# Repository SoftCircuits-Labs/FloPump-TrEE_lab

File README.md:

<h1 align="center">AirFlo-pump</h1>

## About the  AirFlo-Pump Device
It is an air sampler device built for use in the applications that require a regulated air flow, for example sampling of VOCs from plants, room etc., or to generate a regulaed air flow in wind-tunnel experiments.

## Contents
<!---List file contents of the project, in table.--->

| File/folder | Description |
|-------------|-------------|
| `AFC-CODE`       | Firmware for the device |
| `AFC-DOCS`       | Device Images, User's Guide and other documents related to the device|
| `AFC-ENCLOSURE`        | 3D Design files and DXF files for the enclosure |
| `AFC-PCB`         | PCB Schematic files, board files and Gerber files |
| `LICENSE`   | The license for the project. |
| `README.md` | This README file. |

## Built With
* [![Arduino][Arduino-l]][Arduino-url]
* [![Eagle][Eagle-l]][Eagle-url]
* [![Inventor][Inventor-l]][Inventor-url]

## Usage

## Contact 

<!-- MARKDOWN LINKS & IMAGES -->
<!-- https://www.markdownguide.org/basic-syntax/#reference-style-links -->

[Arduino-l]: https://img.shields.io/badge/arduino-00878F?style=for-the-badge&logo=arduino&logoColor=white
[Arduino-url]: https://www.arduino.cc/
[Eagle-l]: https://img.shields.io/badge/Autodesk_Eagle-000000?style=for-the-badge&logo=autodesk&logoColor=white
[Eagle-url]: https://www.autodesk.in/products/eagle/overview
[Inventor-l]: https://img.shields.io/badge/Autodesk_Inventor-000000?style=for-the-badge&logo=autodesk&logoColor=white
[Inventor-url]: https://www.autodesk.in/products/inventor/overview

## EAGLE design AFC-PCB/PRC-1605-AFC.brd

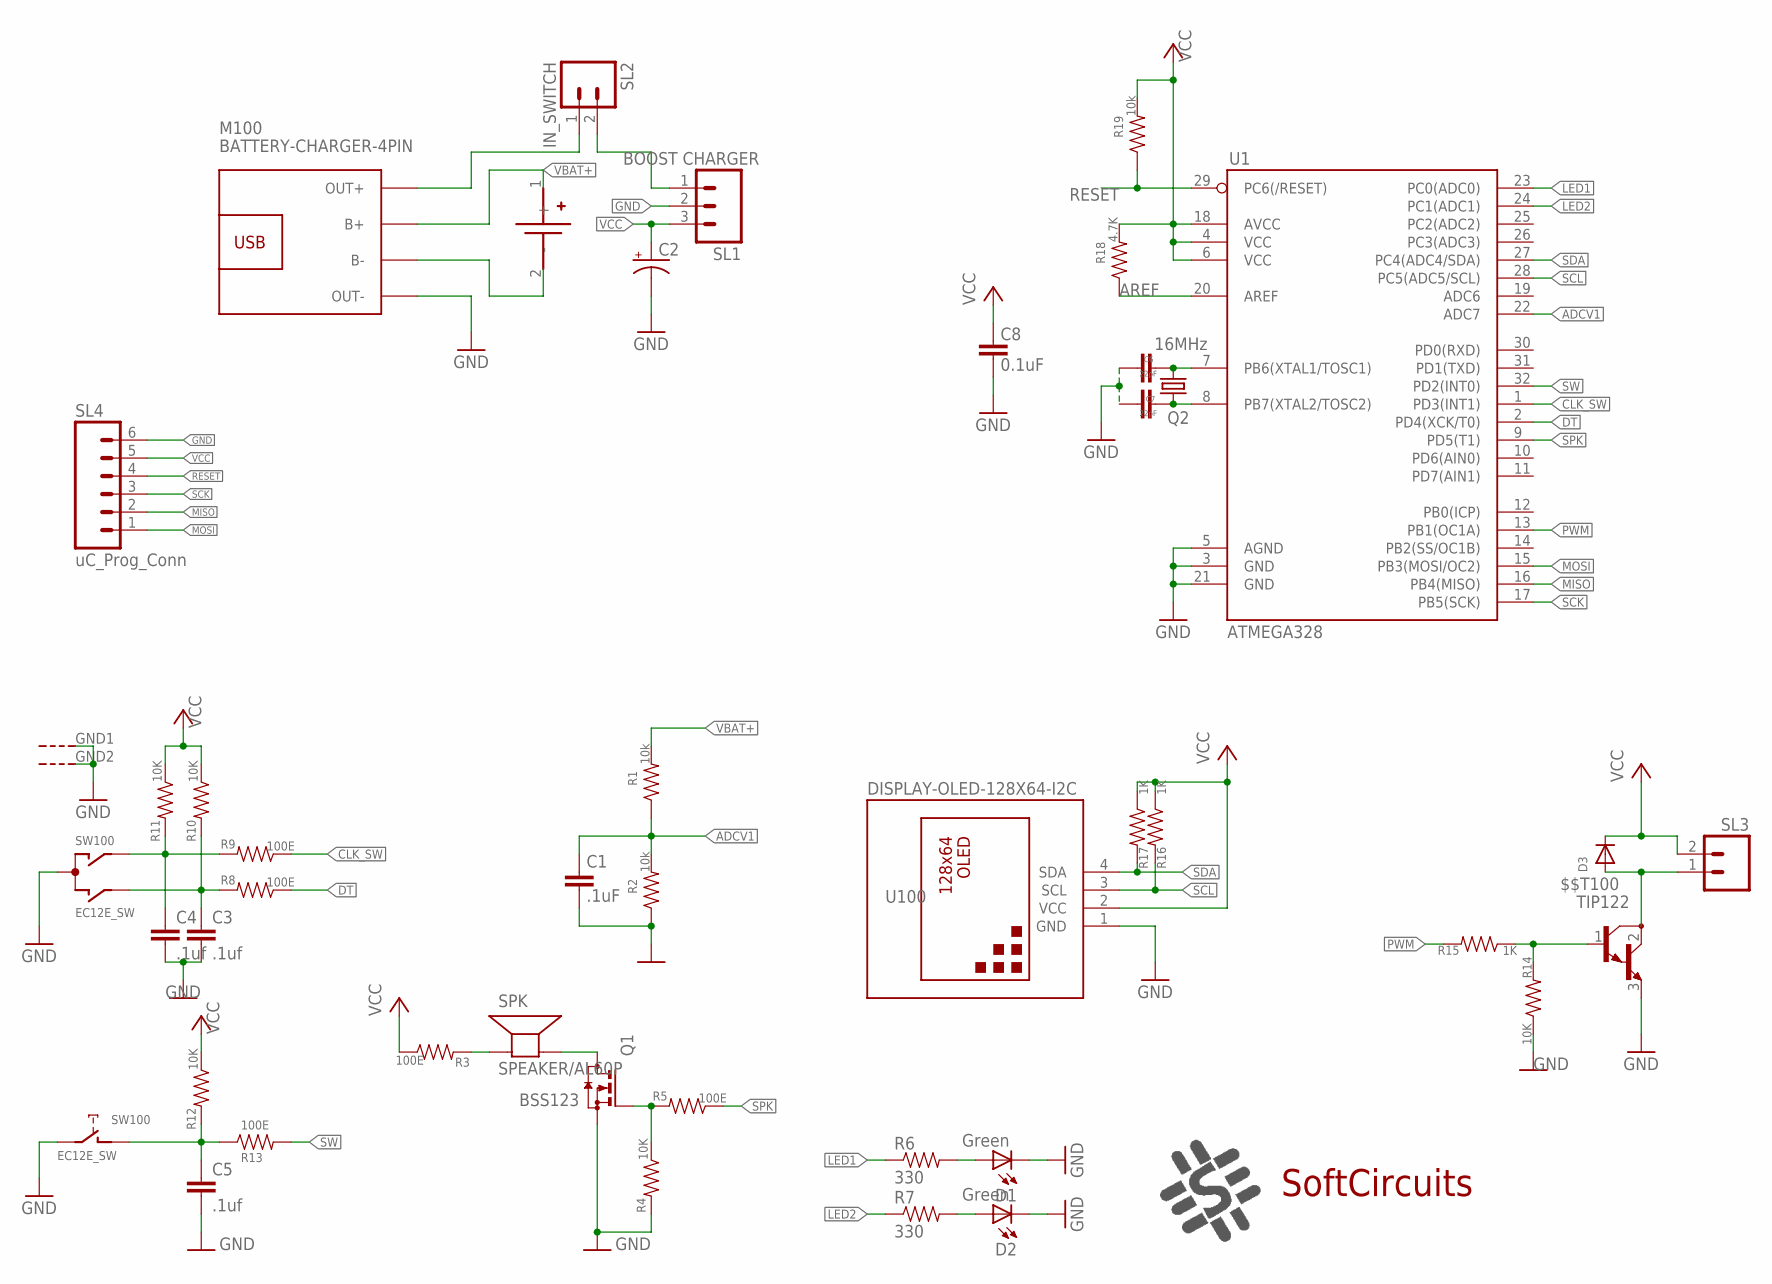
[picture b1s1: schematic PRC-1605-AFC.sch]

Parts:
$$T100: TIP122; TO220
C1: .1uF; C1206
C2: CPOL-USE2.5-7; E2,5-7
C3, C4, C5: .1uf; C1206
C6, C7: 22pF; C1206
C8: 0.1uF; C1206
D1, D2: Green; CHIPLED_1206
D3: DIODESMA; SMADIODE
LOGO100: SC_LOGO
M100: BATTERY-CHARGER-4PIN; BATTERY-CHARGER-LI-4PIN
Q1: BSS123; SOT23
Q2: 16MHz; HC49UP
R1, R2, R19: 10k; 1206
R3, R5, R8, R9, R13: 100E; 1206
R4, R10, R11, R12, R14: 10K; 1206
R6, R7: 330; 1206
R15, R16, R17: 1K; 1206
R18: 4.7K; 1206
SL1: BOOST CHARGER; 03P
SL2: IN_SWITCH; 02P
SL3: M02; 02P
SL4: uC_Prog_Conn; 06P
SPK: SPEAKER/AL60P; AL60P
SW100: EC12E_SW; ALPS_EC12E_SW
U1: ATMEGA328; TQFP32-08
U100: DISPLAY-OLED-128X64-I2C
U$2: BLOSSOM-BLM-18650-1PCS

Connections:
ADCV1: C1.1, R1.1, R2.2, U1.22 (ADC7)
AREF: R18.1, U1.20 (AREF)
CLK_SW: R9.1, U1.1 (PD3(INT1))
DT: R8.1, U1.2 (PD4(XCK/T0))
GND: $$T100.3 (E), C1.2, C2.-, C3.2, C4.2, C5.2, C6.2, C7.2, C8.1, D1.C, D2.C, M100.OUT-, Q1.2 (S), R2.1, R4.2, R14.1, SL1.2, SL4.6, SW100.C, SW100.E (2), SW100.GND1 (G), SW100.GND2 (G), U1.3 (GND), U1.5 (AGND), U1.21 (GND), U100.1 (GND)
LED1: R6.1, U1.23 (PC0(ADC0))
LED2: R7.1, U1.24 (PC1(ADC1))
MISO: SL4.2, U1.16 (PB4(MISO))
MOSI: SL4.1, U1.15 (PB3(MOSI/OC2))
unnamed: R3.2, SPK.1 (+)
unnamed: C5.1, R12.2, R13.1, SW100.D (1)
unnamed: Q1.3 (D), SPK.2 (-)
unnamed: SL1.1, SL2.2
unnamed: C4.1, R9.2, R11.2, SW100.A
unnamed: M100.B-, U$2.2 (-)
unnamed: Q1.1 (G), R4.1, R5.2
unnamed: D2.A, R7.2
unnamed: C3.1, R8.2, R10.2, SW100.B
unnamed: C7.1, Q2.1, U1.8 (PB7(XTAL2/TOSC2))
unnamed: C6.1, Q2.2, U1.7 (PB6(XTAL1/TOSC1))
unnamed: D1.A, R6.2
unnamed: $$T100.1 (B), R14.2, R15.1
unnamed: $$T100.2 (C), D3.A, SL3.1
PWM: R15.2, U1.13 (PB1(OC1A))
RESET: R19.1, SL4.4, U1.29 (PC6(/RESET))
SCK: SL4.3, U1.17 (PB5(SCK))
SCL: R16.2, U1.28 (PC5(ADC5/SCL)), U100.3 (SCL)
SDA: R17.2, U1.27 (PC4(ADC4/SDA)), U100.4 (SDA)
SPK: R5.1, U1.9 (PD5(T1))
SW: R13.2, U1.32 (PD2(INT0))
VBAT+: M100.B+, R1.2, U$2.1 (+)
VCC: C2.+, C8.2, D3.C, R3.1, R10.1, R11.1, R12.1, R16.1, R17.1, R18.2, R19.2, SL1.3, SL3.2, SL4.5, U1.4 (VCC), U1.6 (VCC), U1.18 (AVCC), U100.2 (VCC)
VOUT_CHG: M100.OUT+, SL2.1

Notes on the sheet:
SoftCircuits

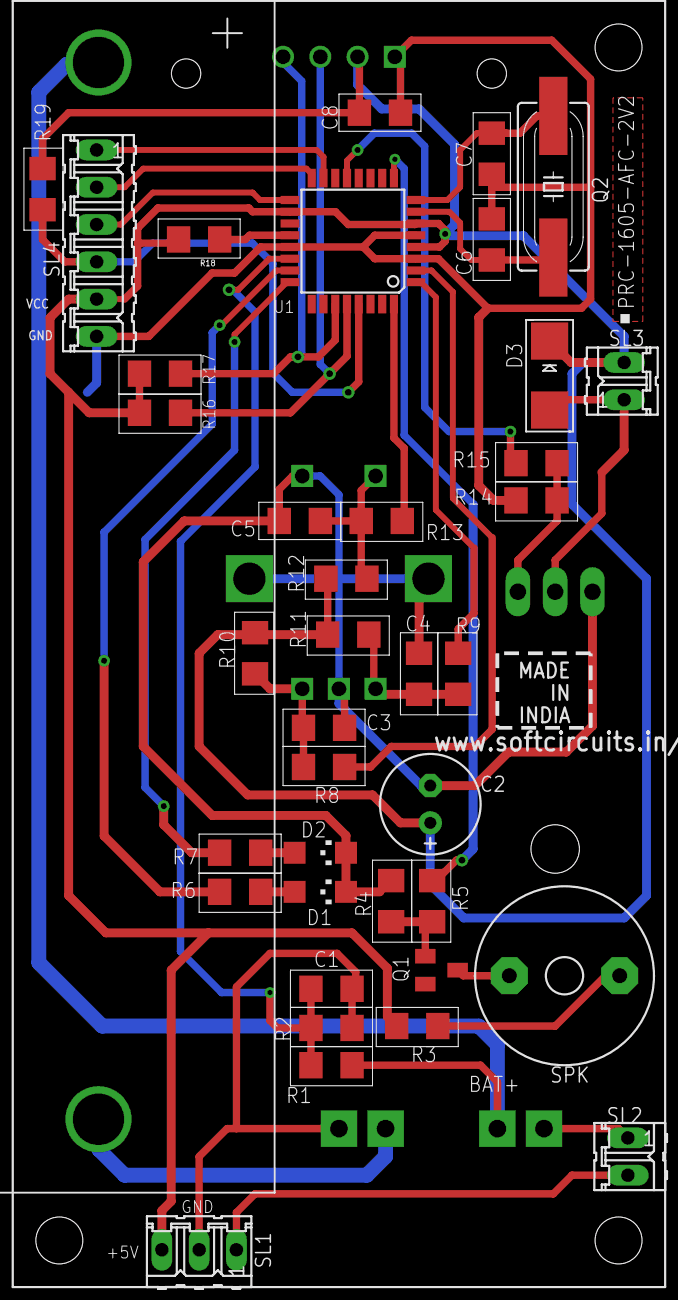
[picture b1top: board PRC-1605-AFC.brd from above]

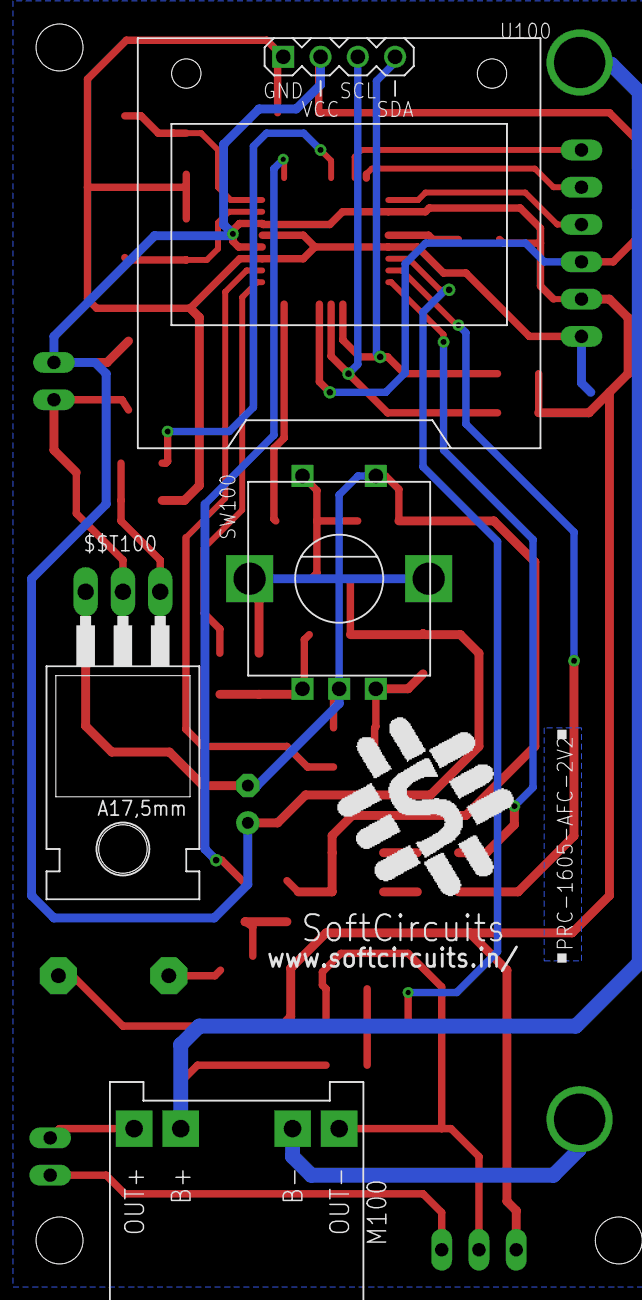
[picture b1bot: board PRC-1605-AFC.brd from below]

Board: 2 copper layers, 44 parts (5 on the bottom side), 33 nets.

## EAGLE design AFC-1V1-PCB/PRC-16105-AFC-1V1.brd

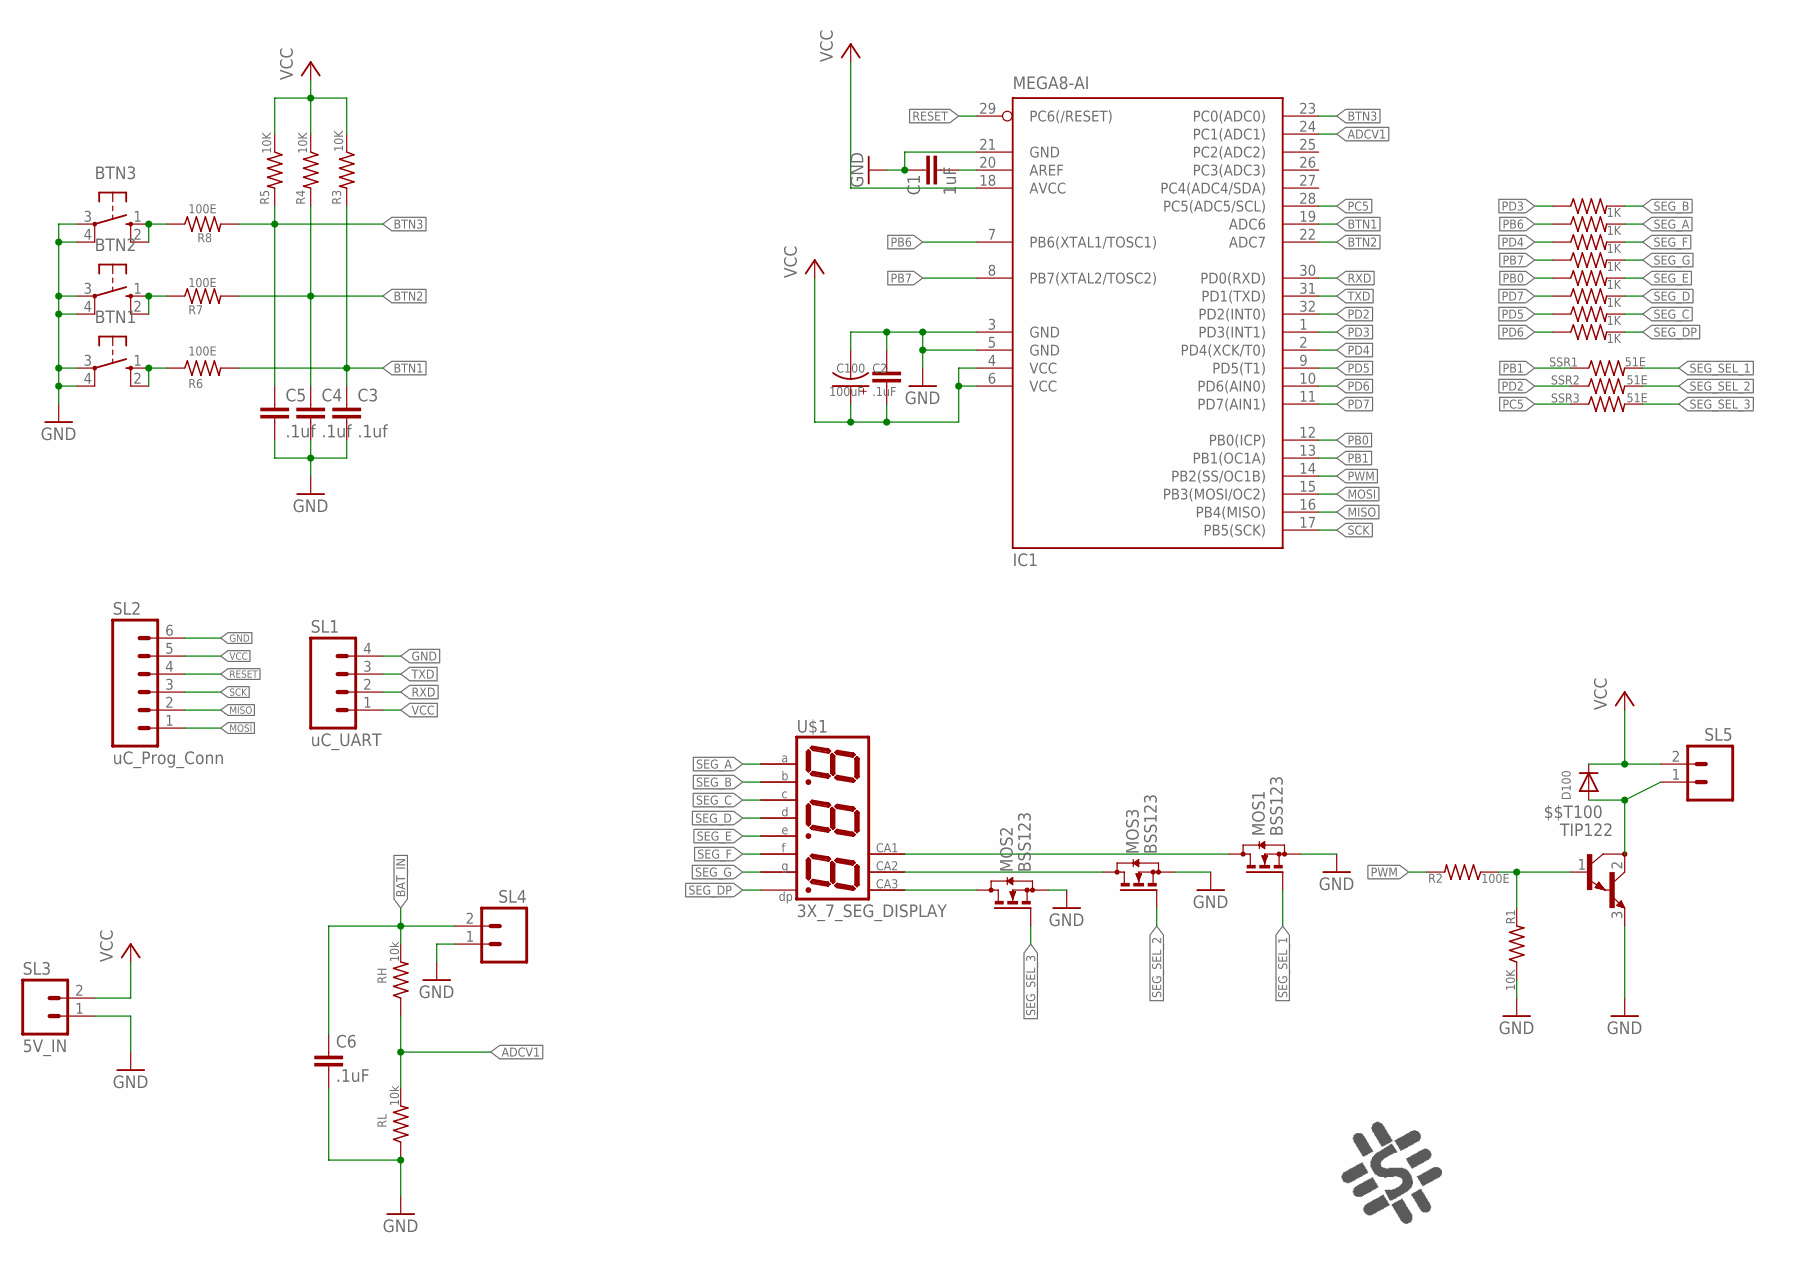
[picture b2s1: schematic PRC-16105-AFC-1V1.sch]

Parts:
$$T100: TIP122; TO220
BTN1, BTN2, BTN3: 10-XX; B3F-10XX
C1: 1uF; C0603K
C2, C6: .1uF; C0603K
C3, C4, C5: .1uf; C0603K
C100: 100uF; 153CLV-0807
D100: DIODESMA; SMADIODE
IC1: MEGA8-AI; TQFP32-08
LOGO100: SC_LOGO
MOS1, MOS2, MOS3: BSS123; SOT23
R1, R3, R4, R5: 10K; R0603
R2, R6, R7, R8: 100E; R0603
RB1, RB2, RB3, RB4, RB5, RB6, RB7, RB8: 1K; R0603
RH: 10k; R0603
RL: 10k; R0603
SL1: uC_UART; 04P
SL2: uC_Prog_Conn; 06P
SL3: 5V_IN; 02P
SL4, SL5: M02; 02P
SSR1, SSR2, SSR3: 51E; R0603
U$1: 3X_7_SEG_DISPLAY; SP36012CR

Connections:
ADCV1: IC1.24 (PC1(ADC1)), RH.1, RL.2
BAT_IN: C6.1, RH.2, SL4.2
BTN1: C3.1, IC1.19 (ADC6), R3.2, R6.2
BTN2: C4.1, IC1.22 (ADC7), R4.2, R7.2
BTN3: C5.1, IC1.23 (PC0(ADC0)), R5.2, R8.2
GND: $$T100.3 (E), BTN1.3, BTN1.4 (P1), BTN2.3, BTN2.4 (P1), BTN3.3, BTN3.4 (P1), C1.1, C2.2, C3.2, C4.2, C5.2, C6.2, C100.-, IC1.3 (GND), IC1.5 (GND), IC1.21 (GND), MOS1.2 (S), MOS2.2 (S), MOS3.2 (S), R1.1, RL.1, SL1.4, SL2.6, SL3.1, SL4.1
MISO: IC1.16 (PB4(MISO)), SL2.2
MOSI: IC1.15 (PB3(MOSI/OC2)), SL2.1
unnamed: BTN1.1 (S), BTN1.2 (S1), R6.1
unnamed: BTN2.1 (S), BTN2.2 (S1), R7.1
unnamed: BTN3.1 (S), BTN3.2 (S1), R8.1
unnamed: C1.2, IC1.20 (AREF)
unnamed: MOS1.3 (D), U$1.12 (CA)
unnamed: MOS3.3 (D), U$1.9 (CA)
unnamed: MOS2.3 (D), U$1.8 (CA)
unnamed: $$T100.1 (B), R1.2, R2.1
unnamed: $$T100.2 (C), D100.A, SL5.1
PB0: IC1.12 (PB0(ICP)), RB1.1
PB1: IC1.13 (PB1(OC1A)), SSR1.1
PB6: IC1.7 (PB6(XTAL1/TOSC1)), RB6.1
PB7: IC1.8 (PB7(XTAL2/TOSC2)), RB5.1
PC5: IC1.28 (PC5(ADC5/SCL)), SSR3.1
PD2: IC1.32 (PD2(INT0)), SSR2.1
PD3: IC1.1 (PD3(INT1)), RB8.1
PD4: IC1.2 (PD4(XCK/T0)), RB7.1
PD5: IC1.9 (PD5(T1)), RB4.1
PD6: IC1.10 (PD6(AIN0)), RB3.1
PD7: IC1.11 (PD7(AIN1)), RB2.1
PWM: IC1.14 (PB2(SS/OC1B)), R2.2
RESET: IC1.29 (PC6(/RESET)), SL2.4
RXD: IC1.30 (PD0(RXD)), SL1.2
SCK: IC1.17 (PB5(SCK)), SL2.3
SEG_A: RB6.2, U$1.11 (A)
SEG_B: RB8.2, U$1.7 (B)
SEG_C: RB4.2, U$1.4 (C)
SEG_D: RB2.2, U$1.2 (D)
SEG_DP: RB3.2, U$1.3 (DP)
SEG_E: RB1.2, U$1.1 (E)
SEG_F: RB7.2, U$1.10 (F)
SEG_G: RB5.2, U$1.5 (G)
SEG_SEL_1: MOS1.1 (G), SSR1.2
SEG_SEL_2: MOS3.1 (G), SSR2.2
SEG_SEL_3: MOS2.1 (G), SSR3.2
TXD: IC1.31 (PD1(TXD)), SL1.3
VCC: C2.1, C100.+, D100.C, IC1.4 (VCC), IC1.6 (VCC), IC1.18 (AVCC), R3.1, R4.1, R5.1, SL1.1, SL2.5, SL3.2, SL5.2

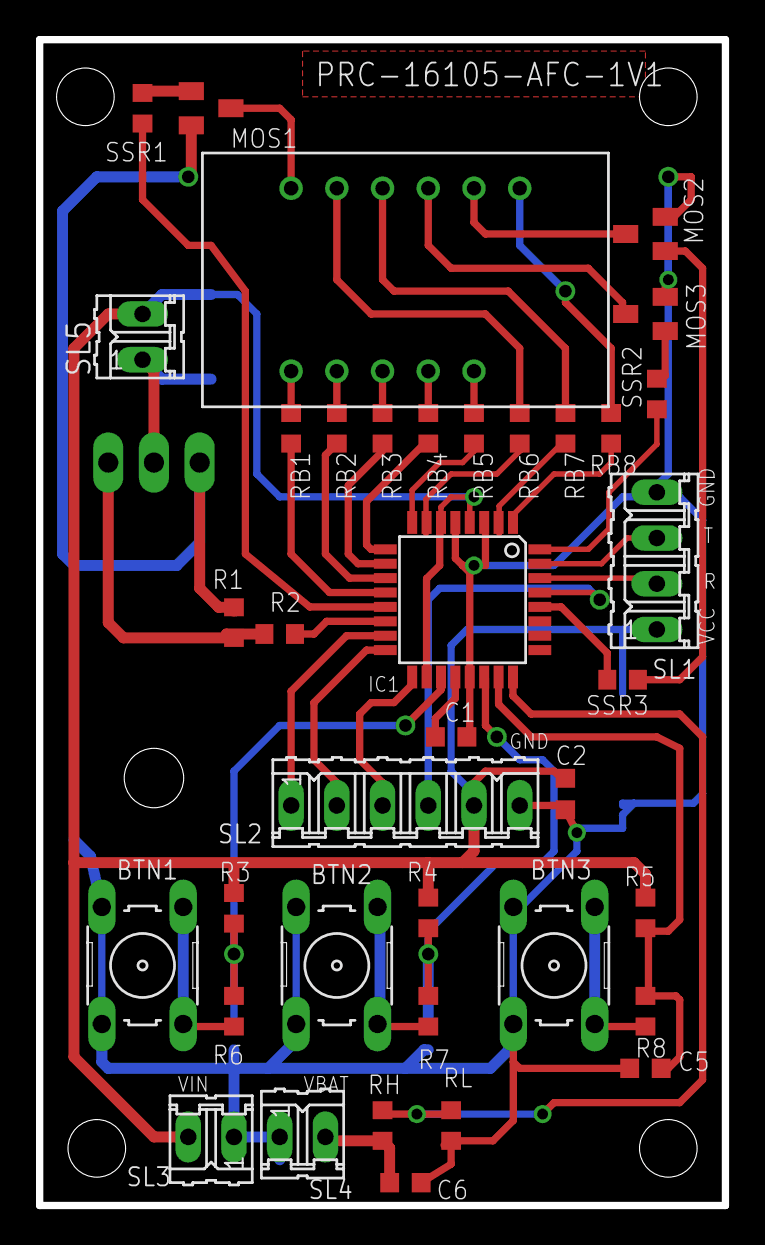
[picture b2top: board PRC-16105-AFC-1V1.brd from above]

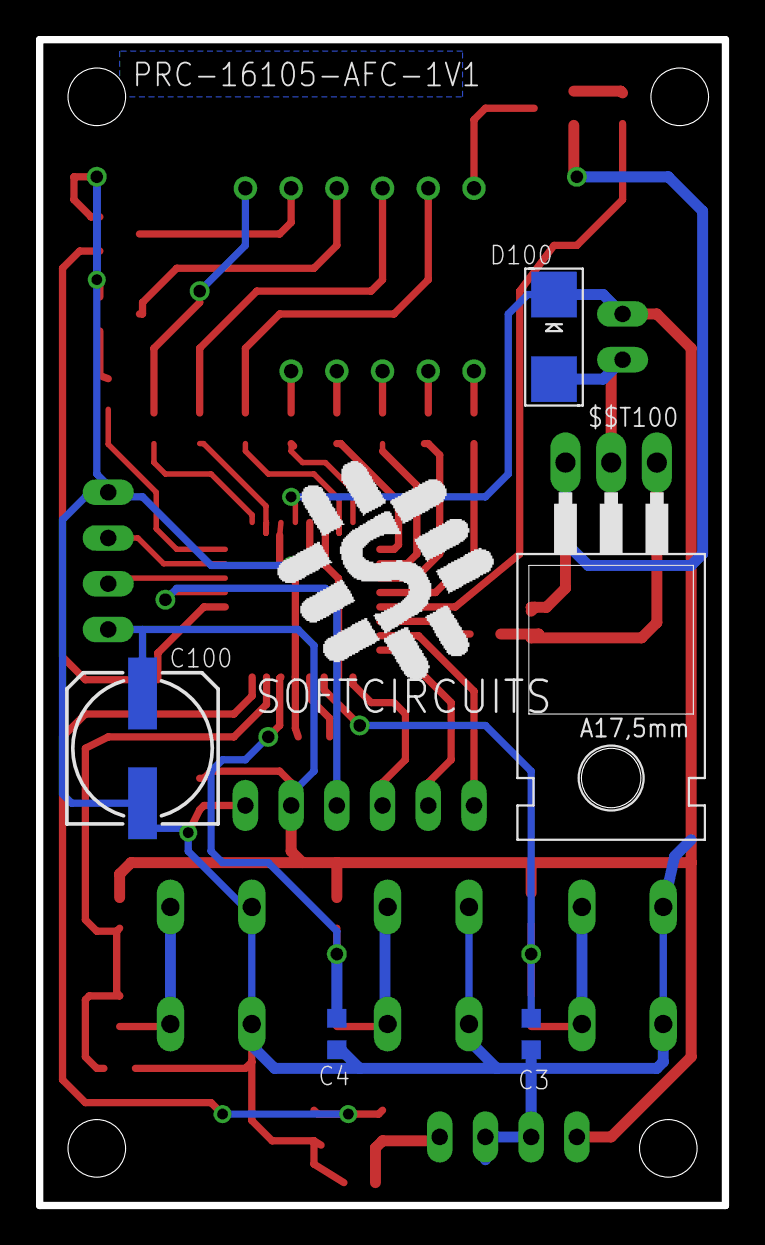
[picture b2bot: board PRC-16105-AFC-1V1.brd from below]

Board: 2 copper layers, 38.1 x 64.8 mm, 44 parts (6 on the bottom side), 45 nets.

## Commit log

2023-09-17 Folder Names Changed for Clarity
2023-09-17 Updated the hardware design
    Updated the hardware to the latest version.
2023-10-02 Updated 3D Files and Arduino code for latest version

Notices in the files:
parts and their libraries:
diy-modules1.8: Released under the Creative Commons Attribution 4.0 International License: http://creativecommons.org/licenses/by/4.0
SoftCircuits-Resistors: Licensing: Creative Commons ShareAlike 4.0 International - https://creativecommons.org/licenses/by-sa/4.0
